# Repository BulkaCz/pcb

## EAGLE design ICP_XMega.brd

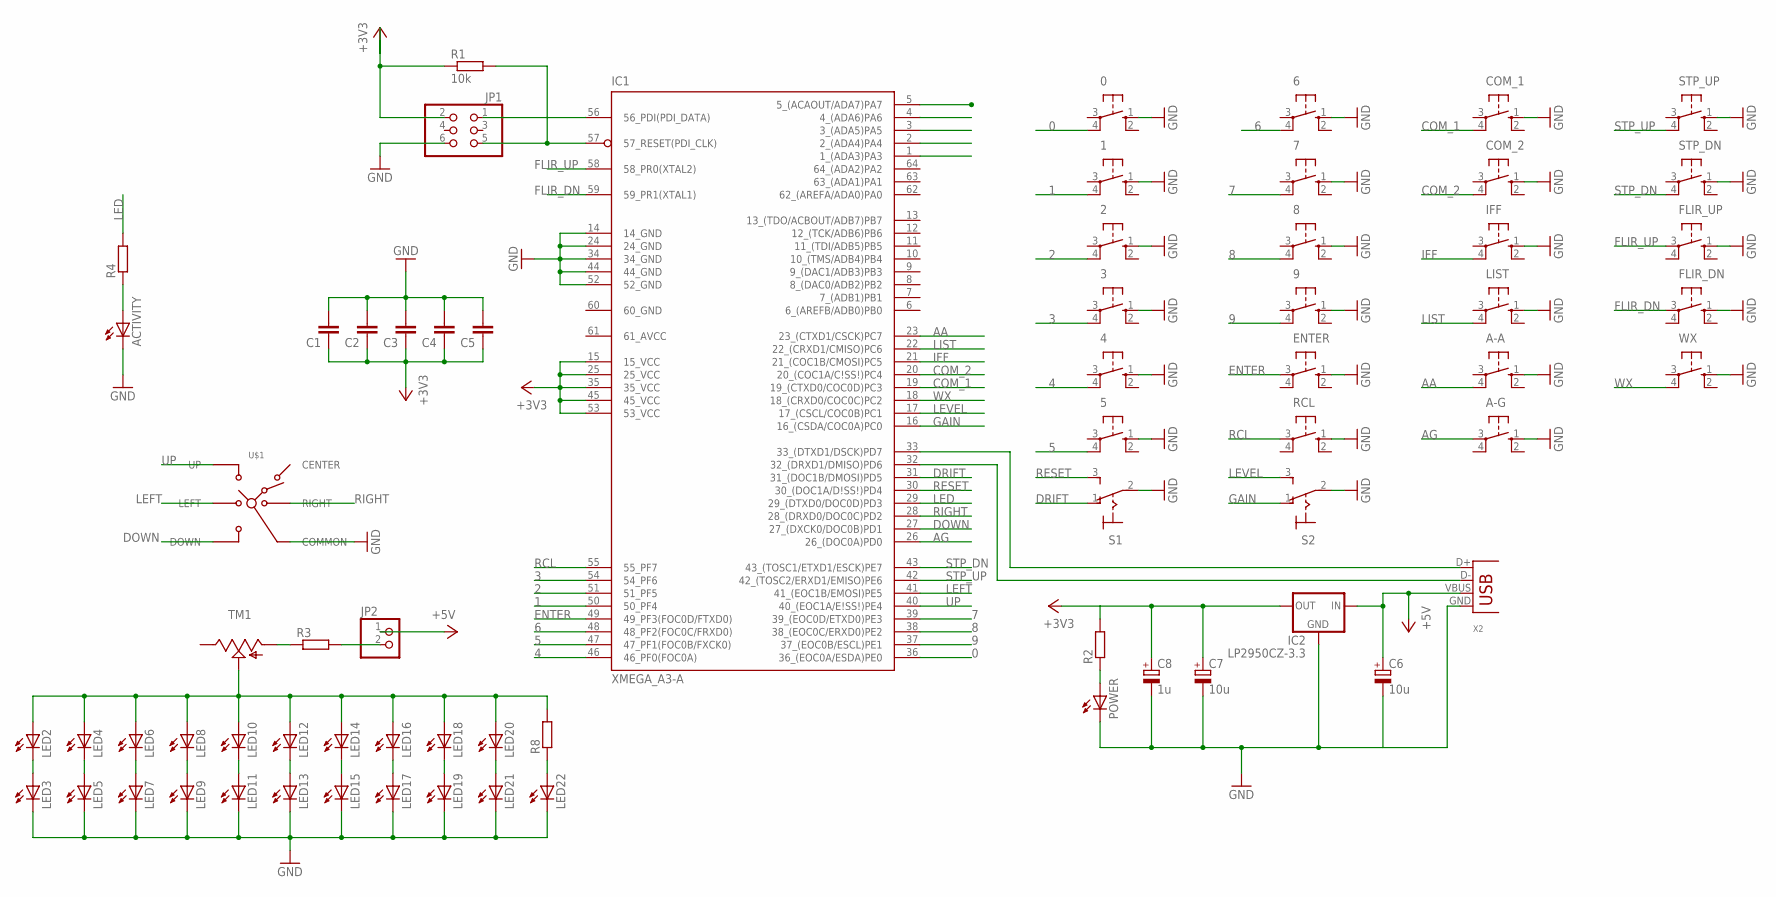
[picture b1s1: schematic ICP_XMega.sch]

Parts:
0, 1, 2, 3, 4, 5, 6, 7, 8, 9: 10-XX; B3F-10XX
A-A: 10-XX; B3F-10XX
A-G: 10-XX; B3F-10XX
ACTIVITY: LEDSMT1206; 1206
C1, C2, C3, C4, C5: C-EUC1206; C1206
C6, C7: 10u; E2,5-5
C8: 1u; C/6032-28R
COM_1, COM_2: 10-XX; B3F-10XX
ENTER: 10-XX; B3F-10XX
FLIR_DN: 10-XX; B3F-10XX
FLIR_UP: 10-XX; B3F-10XX
IC1: XMEGA_A3-A; TQFP64
IC2: LP2950CZ-3.3; TO92
IFF: 10-XX; B3F-10XX
JP1: PINHD-2X3; 2X03
JP2: PINHD-1X2; 1X02
LED2, LED3, LED4, LED5, LED6, LED7, LED8, LED9, LED10, LED11, LED12, LED13, LED14, LED15, LED16, LED17, LED18, LED19, LED20, LED21, LED22: LEDSMT1206; 1206
LIST: 10-XX; B3F-10XX
POWER: LEDSMT1206; 1206
R1: 10k; R1206
R2, R4, R8: R-EU_M1206; M1206
R3: R-EU_0204/7; 0204/7
RCL: 10-XX; B3F-10XX
S1, S2: 320-916
STP_DN: 10-XX; B3F-10XX
STP_UP: 10-XX; B3F-10XX
TM1: TRIM; 6MM
U$1: SKQUCAA010; SKQU
WX: 10-XX; B3F-10XX
X2: USB-B-H

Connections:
0: 0.4 (P1), IC1.36 (36_(EOC0A/ESDA)PE0)
1: 1.4 (P1), IC1.50 (50_PF4)
2: 2.4 (P1), IC1.51 (51_PF5)
3: 3.4 (P1), IC1.54 (54_PF6)
4: 4.4 (P1), IC1.46 (46_PF0(FOC0A))
5: 5.4 (P1), IC1.47 (47_PF1(FOC0B/FXCK0))
6: 6.4 (P1), IC1.48 (48_PF2(FOC0C/FRXD0))
7: 7.4 (P1), IC1.39 (39_(EOC0D/ETXD0)PE3)
8: 8.4 (P1), IC1.38 (38_(EOC0C/ERXD0)PE2)
9: 9.4 (P1), IC1.37 (37_(EOC0B/ESCL)PE1)
+3V3: C1.1, C2.1, C3.1, C4.1, C5.1, C7.+, C8.+, IC1.15 (15_VCC), IC1.25 (25_VCC), IC1.35 (35_VCC), IC1.45 (45_VCC), IC1.53 (53_VCC), IC2.1 (OUT), JP1.2, R1.1, R2.2
+5V: C6.+, IC2.3 (IN), JP2.1, X2.VBUS
AA: A-A.4 (P1), IC1.23 (23_(CTXD1/CSCK)PC7)
AG: A-G.3, IC1.26 (26_(DOC0A)PD0)
COM_1: COM_1.4 (P1), IC1.19 (19_(CTXD0/COC0D)PC3)
COM_2: COM_2.4 (P1), IC1.20 (20_(COC1A/C\!SS\!)PC4)
DOWN: IC1.27 (27_(DXCK0/DOC0B)PD1), U$1.DOWN
DRIFT: IC1.31 (31_(DOC1B/DMOSI)PD5), S1.1 (O)
ENTER: ENTER.3, IC1.49 (49_PF3(FOC0D/FTXD0))
FLIR_DN: FLIR_DN.3, IC1.59 (59_PR1(XTAL1))
FLIR_UP: FLIR_UP.3, IC1.58 (58_PR0(XTAL2))
GAIN: IC1.16 (16_(CSDA/COC0A)PC0), S2.1 (O)
GND: 0.1 (S), 1.1 (S), 2.1 (S), 3.1 (S), 4.1 (S), 5.1 (S), 6.1 (S), 7.1 (S), 8.1 (S), 9.1 (S), A-A.1 (S), A-G.1 (S), ACTIVITY.C, C1.2, C2.2, C3.2, C4.2, C5.2, C6.-, C7.-, C8.-, COM_1.1 (S), COM_2.1 (S), ENTER.1 (S), FLIR_DN.1 (S), FLIR_UP.1 (S), IC1.14 (14_GND), IC1.24 (24_GND), IC1.34 (34_GND), IC1.44 (44_GND), IC1.52 (52_GND), IC2.2 (GND), IFF.1 (S), JP1.6, LED3.C, LED5.C, LED7.C, LED9.C, LED11.C, LED13.C, LED15.C, LED17.C, LED19.C, LED21.C, LED22.C, LIST.1 (S), POWER.C, RCL.1 (S), S1.2, S2.2, STP_DN.1 (S), STP_UP.1 (S), U$1.COMMON, WX.1 (S), X2.GND
IFF: IC1.21 (21_(COC1B/CMOSI)PC5), IFF.4 (P1)
LED: IC1.29 (29_(DTXD0/DOC0D)PD3), R4.2
LEFT: IC1.41 (41_(EOC1B/EMOSI)PE5), U$1.LEFT
LEVEL: IC1.17 (17_(CSCL/COC0B)PC1), S2.3 (S)
LIST: IC1.22 (22_(CRXD1/CMISO)PC6), LIST.4 (P1)
unnamed: IC1.56 (56_PDI(PDI_DATA)), JP1.1
unnamed: IC1.57 (57_RESET(PDI_CLK)), JP1.5, R1.2
unnamed: IC1.33 (33_(DTXD1/DSCK)PD7), X2.D+
unnamed: LED22.A, R8.1
unnamed: IC1.32 (32_(DRXD1/DMISO)PD6), X2.D-
unnamed: POWER.A, R2.1
unnamed: LED18.C, LED19.A
unnamed: LED20.C, LED21.A
unnamed: LED16.C, LED17.A
unnamed: LED14.C, LED15.A
unnamed: LED12.C, LED13.A
unnamed: LED10.C, LED11.A
unnamed: LED8.C, LED9.A
unnamed: LED6.C, LED7.A
unnamed: LED4.C, LED5.A
unnamed: LED2.C, LED3.A
unnamed: R3.1, TM1.A
unnamed: LED2.A, LED4.A, LED6.A, LED8.A, LED10.A, LED12.A, LED14.A, LED16.A, LED18.A, LED20.A, R8.2, TM1.S
unnamed: JP2.2, R3.2
unnamed: ACTIVITY.A, R4.1
RCL: IC1.55 (55_PF7), RCL.3
RESET: IC1.30 (30_(DOC1A/D\!SS\!)PD4), S1.3 (S)
RIGHT: IC1.28 (28_(DRXD0/DOC0C)PD2), U$1.RIGHT
STP_DN: IC1.43 (43_(TOSC1/ETXD1/ESCK)PE7), STP_DN.4 (P1)
STP_UP: IC1.42 (42_(TOSC2/ERXD1/EMISO)PE6), STP_UP.4 (P1)
UP: IC1.40 (40_(EOC1A/E\!SS\!)PE4), U$1.UP
WX: IC1.18 (18_(CRXD0/COC0C)PC2), WX.4 (P1)

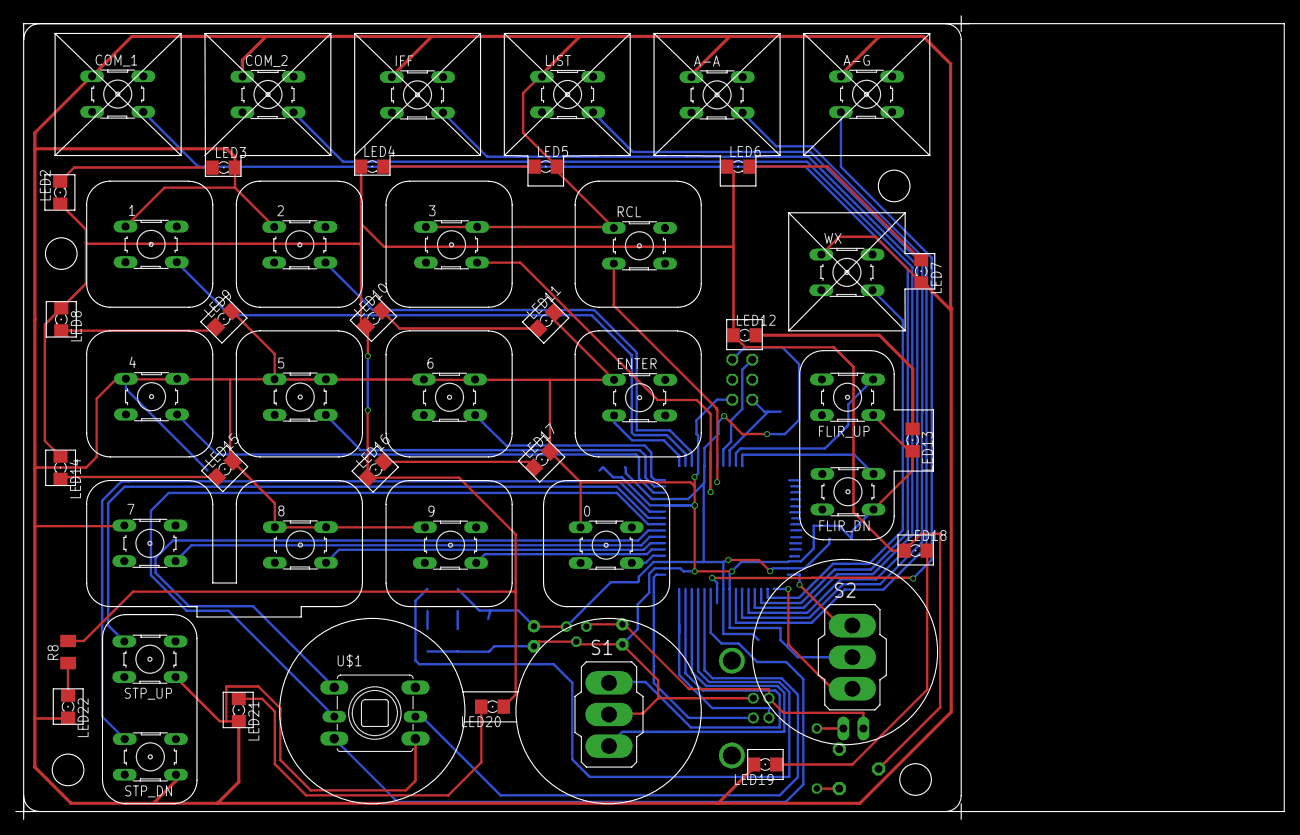
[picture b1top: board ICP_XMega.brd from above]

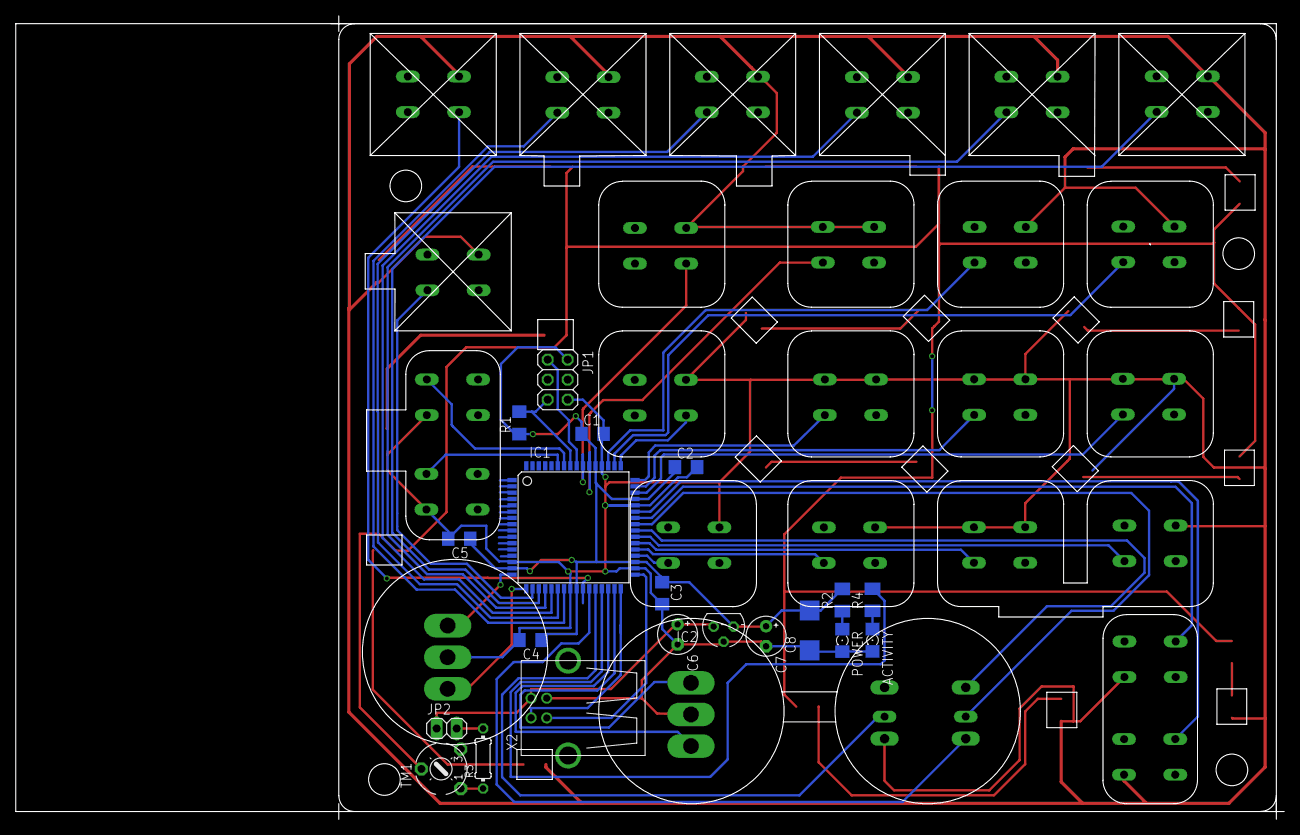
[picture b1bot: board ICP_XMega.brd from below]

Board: 2 copper layers, 161.0 x 102.0 mm, 68 parts (20 on the bottom side), 55 nets.

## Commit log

2015-03-21 :lollipop: Added .gitattributes & .gitignore files
2015-04-26 df
    fsfsfsfa
